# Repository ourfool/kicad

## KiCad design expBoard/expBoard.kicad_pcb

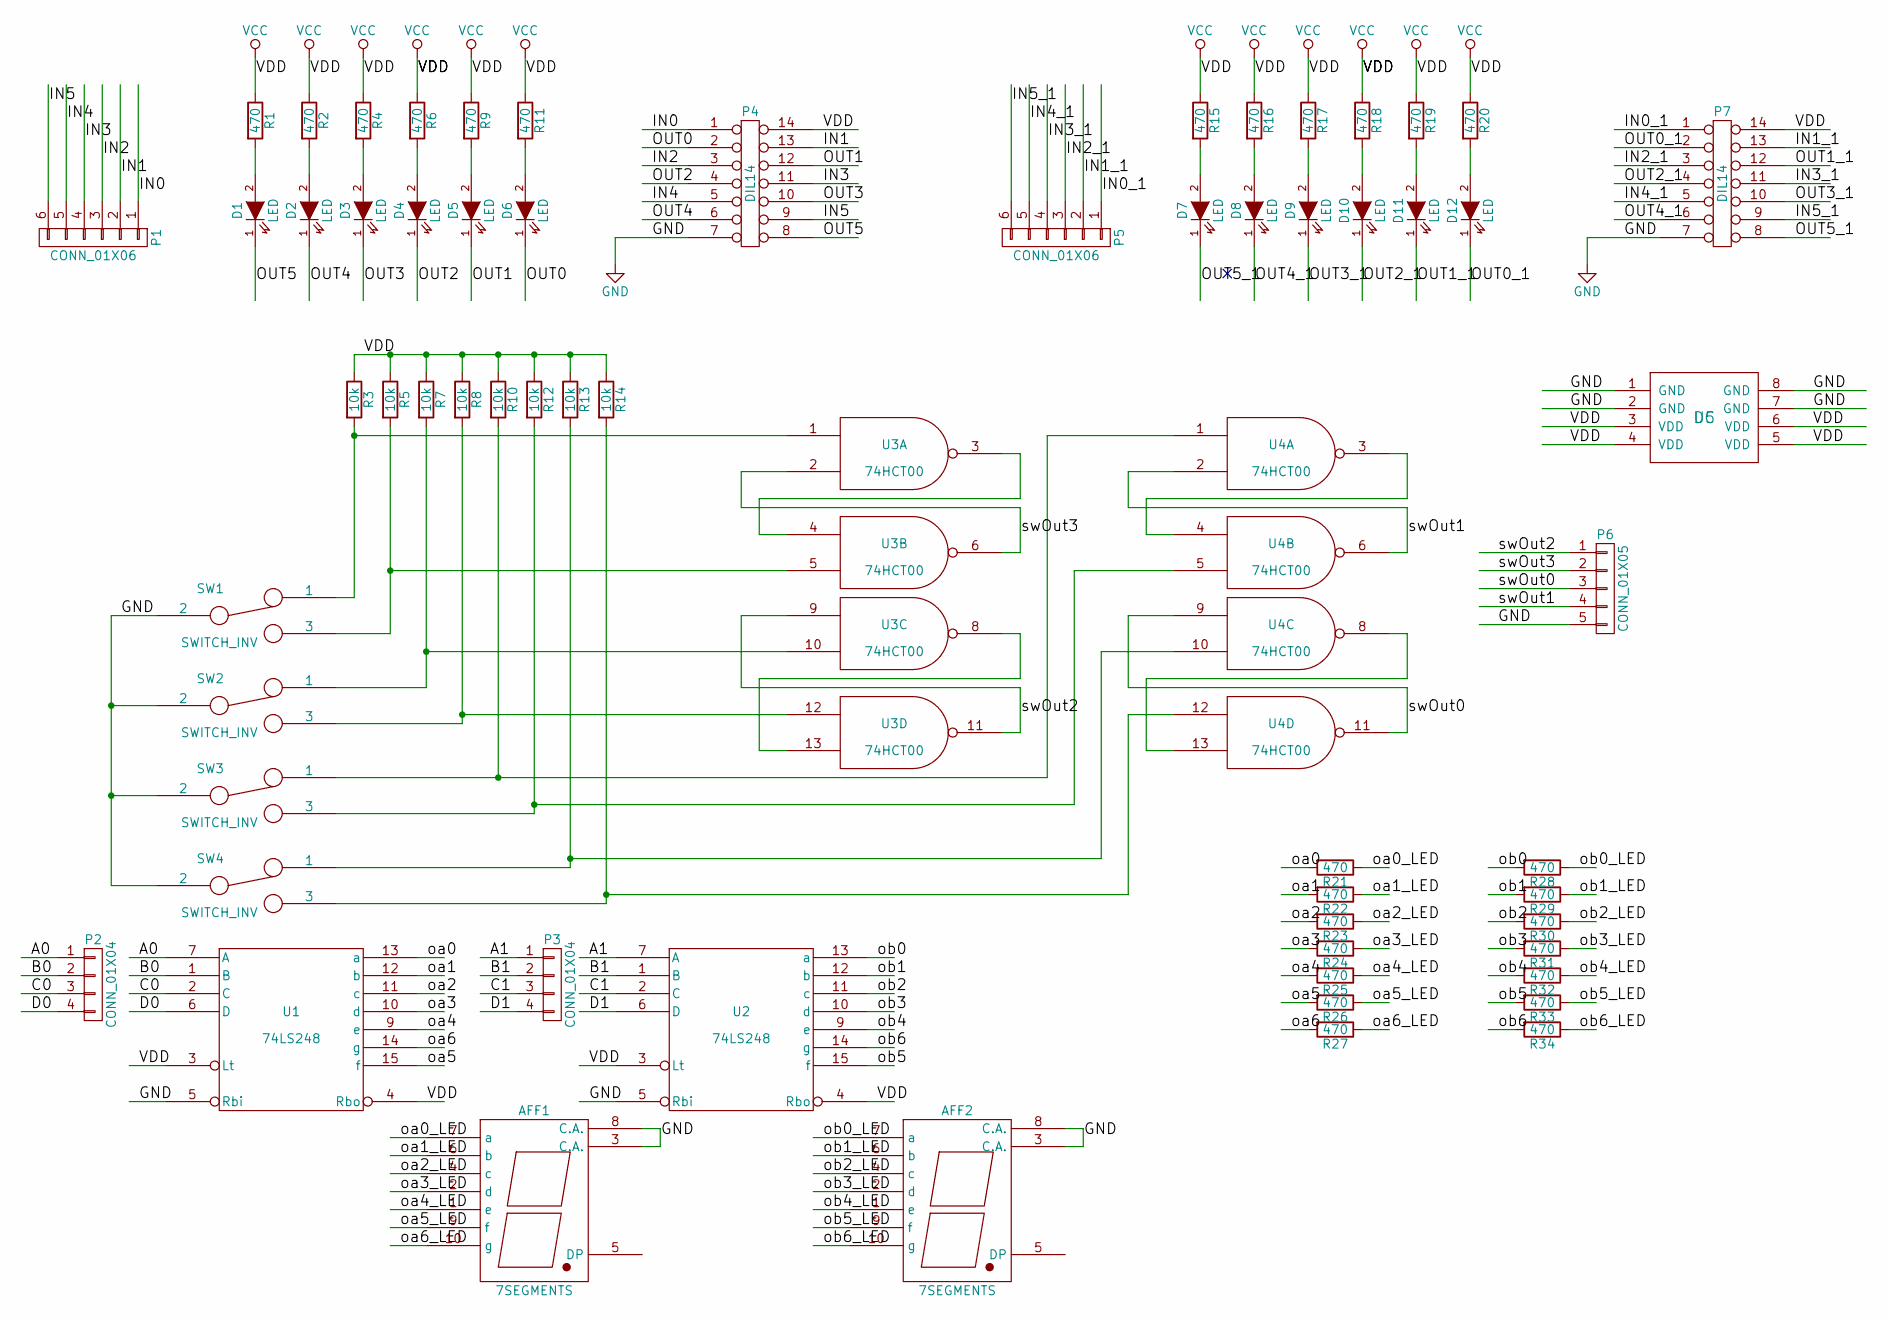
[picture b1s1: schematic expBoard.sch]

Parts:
AFF1, AFF2: 7SEGMENTS; 7SegmentLED_LTS6760_LTS6780
D1, D2, D3, D4, D5, D6, D7, D8, D9, D10, D11, D12: LED; D_A-405_P2.54mm_Vertical_KathodeUp
P1, P5: CONN_01X06; Pin_Header_Straight_1x06_Pitch2.54mm
P2, P3: CONN_01X04; Pin_Header_Straight_1x04_Pitch2.54mm
P4, P7: DIL14; DIP-14_W7.62mm
P6: CONN_01X05; Pin_Header_Straight_1x05_Pitch2.54mm
R1, R2, R4, R6, R9, R11, R15, R16, R17, R18, R19, R20, R21, R22, R23, R24, R25, R26, R27, R28, R29, R30, R31, R32, R33, R34: 470; R_Axial_DIN0207_L6.3mm_D2.5mm_P10.16mm_Horizontal
R3, R5, R7, R8, R10, R12, R13, R14: 10k; R_Axial_DIN0207_L6.3mm_D2.5mm_P10.16mm_Horizontal
SW1, SW2, SW3, SW4: SWITCH_INV; Pin_Header_Straight_1x03_Pitch2.54mm
U1, U2: 74LS248; DIP-16_W7.62mm_Socket
U3, U4: 74HCT00; DIP-14_W7.62mm
U5: DC

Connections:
/A0: P2.1, U1.7 (A)
/A1: P3.1, U2.7 (A)
/B0: P2.2, U1.1 (B)
/B1: P3.2, U2.1 (B)
/C0: P2.3, U1.2 (C)
/C1: P3.3, U2.2 (C)
/D0: P2.4, U1.6 (D)
/D1: P3.4, U2.6 (D)
/IN0: P1.1, P4.1
/IN0_1: P5.1, P7.1
/IN1: P1.2, P4.13
/IN1_1: P5.2, P7.13
/IN2: P1.3, P4.3
/IN2_1: P5.3, P7.3
/IN3: P1.4, P4.11
/IN3_1: P5.4, P7.11
/IN4: P1.5, P4.5
/IN4_1: P5.5, P7.5
/IN5: P1.6, P4.9
/IN5_1: P5.6, P7.9
/OUT0: D6.1 (K), P4.2
/OUT0_1: D12.1 (K), P7.2
/OUT1: D5.1 (K), P4.12
/OUT1_1: D11.1 (K), P7.12
/OUT2: D4.1 (K), P4.4
/OUT2_1: D10.1 (K), P7.4
/OUT3: D3.1 (K), P4.10
/OUT3_1: D9.1 (K), P7.10
/OUT4: D2.1 (K), P4.6
/OUT4_1: D8.1 (K), P7.6
/OUT5: D1.1 (K), P4.8
/OUT5_1: D7.1 (K), P7.8
/oa0: R21.2, U1.13 (a)
/oa0_LED: AFF1.7 (a), R21.1
/oa1: R22.2, U1.12 (b)
/oa1_LED: AFF1.6 (b), R22.1
/oa2: R23.2, U1.11 (c)
/oa2_LED: AFF1.4 (c), R23.1
/oa3: R24.2, U1.10 (d)
/oa3_LED: AFF1.2 (d), R24.1
/oa4: R25.2, U1.9 (e)
/oa4_LED: AFF1.1 (e), R25.1
/oa5: R26.2, U1.15 (f)
/oa5_LED: AFF1.9 (f), R26.1
/oa6: R27.2, U1.14 (g)
/oa6_LED: AFF1.10 (g), R27.1
/ob0: R28.2, U2.13 (a)
/ob0_LED: AFF2.7 (a), R28.1
/ob1: R29.2, U2.12 (b)
/ob1_LED: AFF2.6 (b), R29.1
/ob2: R30.2, U2.11 (c)
/ob2_LED: AFF2.4 (c), R30.1
/ob3: R31.2, U2.10 (d)
/ob3_LED: AFF2.2 (d), R31.1
/ob4: R32.2, U2.9 (e)
/ob4_LED: AFF2.1 (e), R32.1
/ob5: R33.2, U2.15 (f)
/ob5_LED: AFF2.9 (f), R33.1
/ob6: R34.2, U2.14 (g)
/ob6_LED: AFF2.10 (g), R34.1
/swOut0: P6.3, U4.9, U4.11
/swOut1: P6.4, U4.2, U4.6
/swOut2: P6.1, U3.9, U3.11
/swOut3: P6.2, U3.2, U3.6
GND: AFF1.3 (C.A.), AFF1.8 (C.A.), AFF2.3 (C.A.), AFF2.8 (C.A.), P4.7, P6.5, P7.7, SW1.2, SW2.2, SW3.2, SW4.2, U1.5 (Rbi), U1.8 (GND), U2.5 (Rbi), U2.8 (GND), U3.7 (GND), U4.7 (GND), U5.1 (GND), U5.2 (GND), U5.7 (GND), U5.8 (GND)
unnamed: D1.2 (A), R1.2
unnamed: D2.2 (A), R2.2
unnamed: D3.2 (A), R4.2
unnamed: D4.2 (A), R6.2
unnamed: D5.2 (A), R9.2
unnamed: D6.2 (A), R11.2
unnamed: D7.2 (A), R15.2
unnamed: D8.2 (A), R16.2
unnamed: D9.2 (A), R17.2
unnamed: D10.2 (A), R18.2
unnamed: D11.2 (A), R19.2
unnamed: D12.2 (A), R20.2
unnamed: R3.2, SW1.1, U3.1
unnamed: R5.2, SW1.3, U3.5
unnamed: R7.2, SW2.1, U3.10
unnamed: R8.2, SW2.3, U3.12
unnamed: R10.2, SW3.1, U4.1
unnamed: R12.2, SW3.3, U4.5
unnamed: R13.2, SW4.1, U4.10
unnamed: R14.2, SW4.3, U4.12
unnamed: U3.3, U3.4
unnamed: U3.8, U3.13
unnamed: U4.3, U4.4
unnamed: U4.8, U4.13
VCC: P4.14, P7.14, R1.1, R2.1, R3.1, R4.1, R5.1, R6.1, R7.1, R8.1, R9.1, R10.1, R11.1, R12.1, R13.1, R14.1, R15.1, R16.1, R17.1, R18.1, R19.1, R20.1, U1.3 (Lt), U1.4 (Rbo), U1.16 (VCC), U2.3 (Lt), U2.4 (Rbo), U2.16 (VCC), U3.14 (VCC), U4.14 (VCC), U5.3 (VDD), U5.4 (VDD), U5.5 (VDD), U5.6 (VDD)

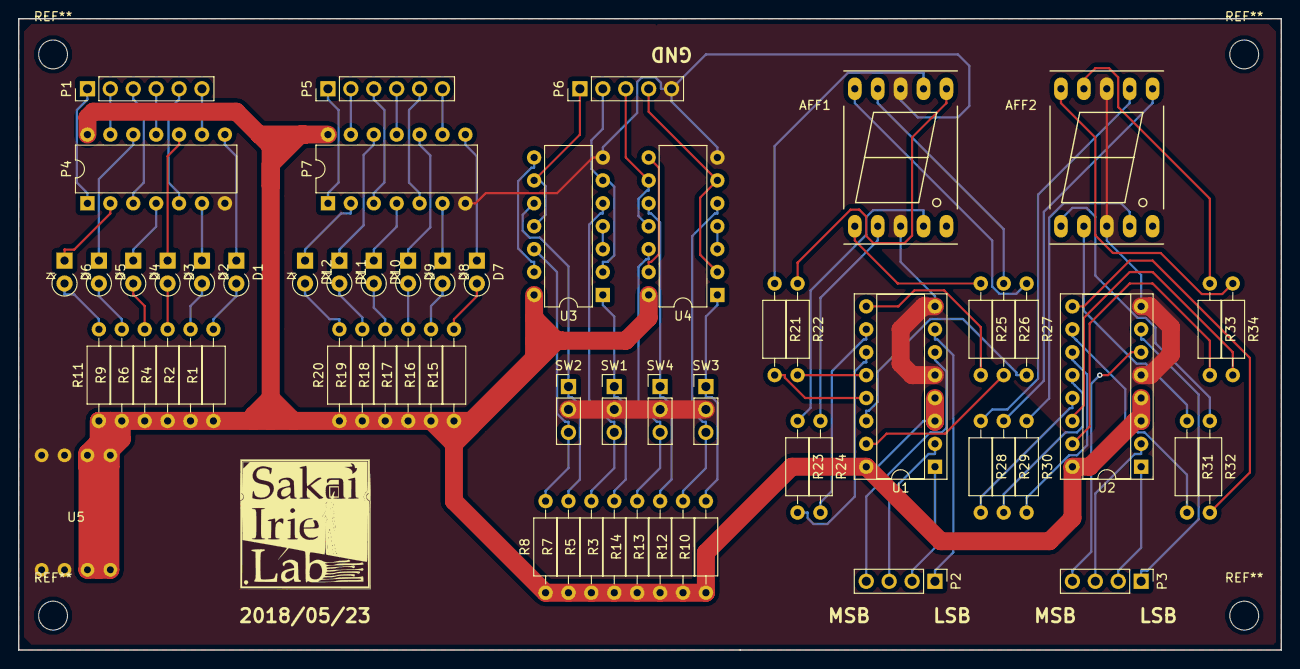
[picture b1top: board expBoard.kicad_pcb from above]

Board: 2 copper layers, 140.0 x 70.0 mm, 64 parts (0 on the bottom side), 90 nets.

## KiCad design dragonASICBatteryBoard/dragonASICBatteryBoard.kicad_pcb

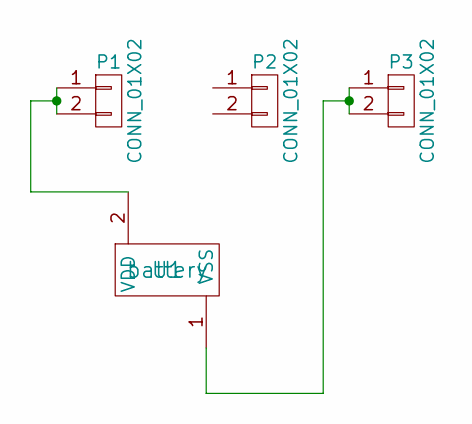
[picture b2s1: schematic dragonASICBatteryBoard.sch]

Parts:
P1, P2, P3: CONN_01X02; Pin_Header_Straight_1x02_Pitch2.54mm
U1: battery

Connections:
unnamed: P1.1, P1.2, U1.2 (VDD)
unnamed: P3.1, P3.2, U1.1 (VSS)

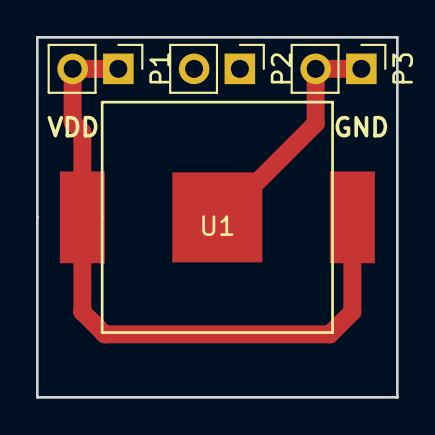
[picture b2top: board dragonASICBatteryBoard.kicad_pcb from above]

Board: 2 copper layers, 20.0 x 20.0 mm, 4 parts (0 on the bottom side), 2 nets.

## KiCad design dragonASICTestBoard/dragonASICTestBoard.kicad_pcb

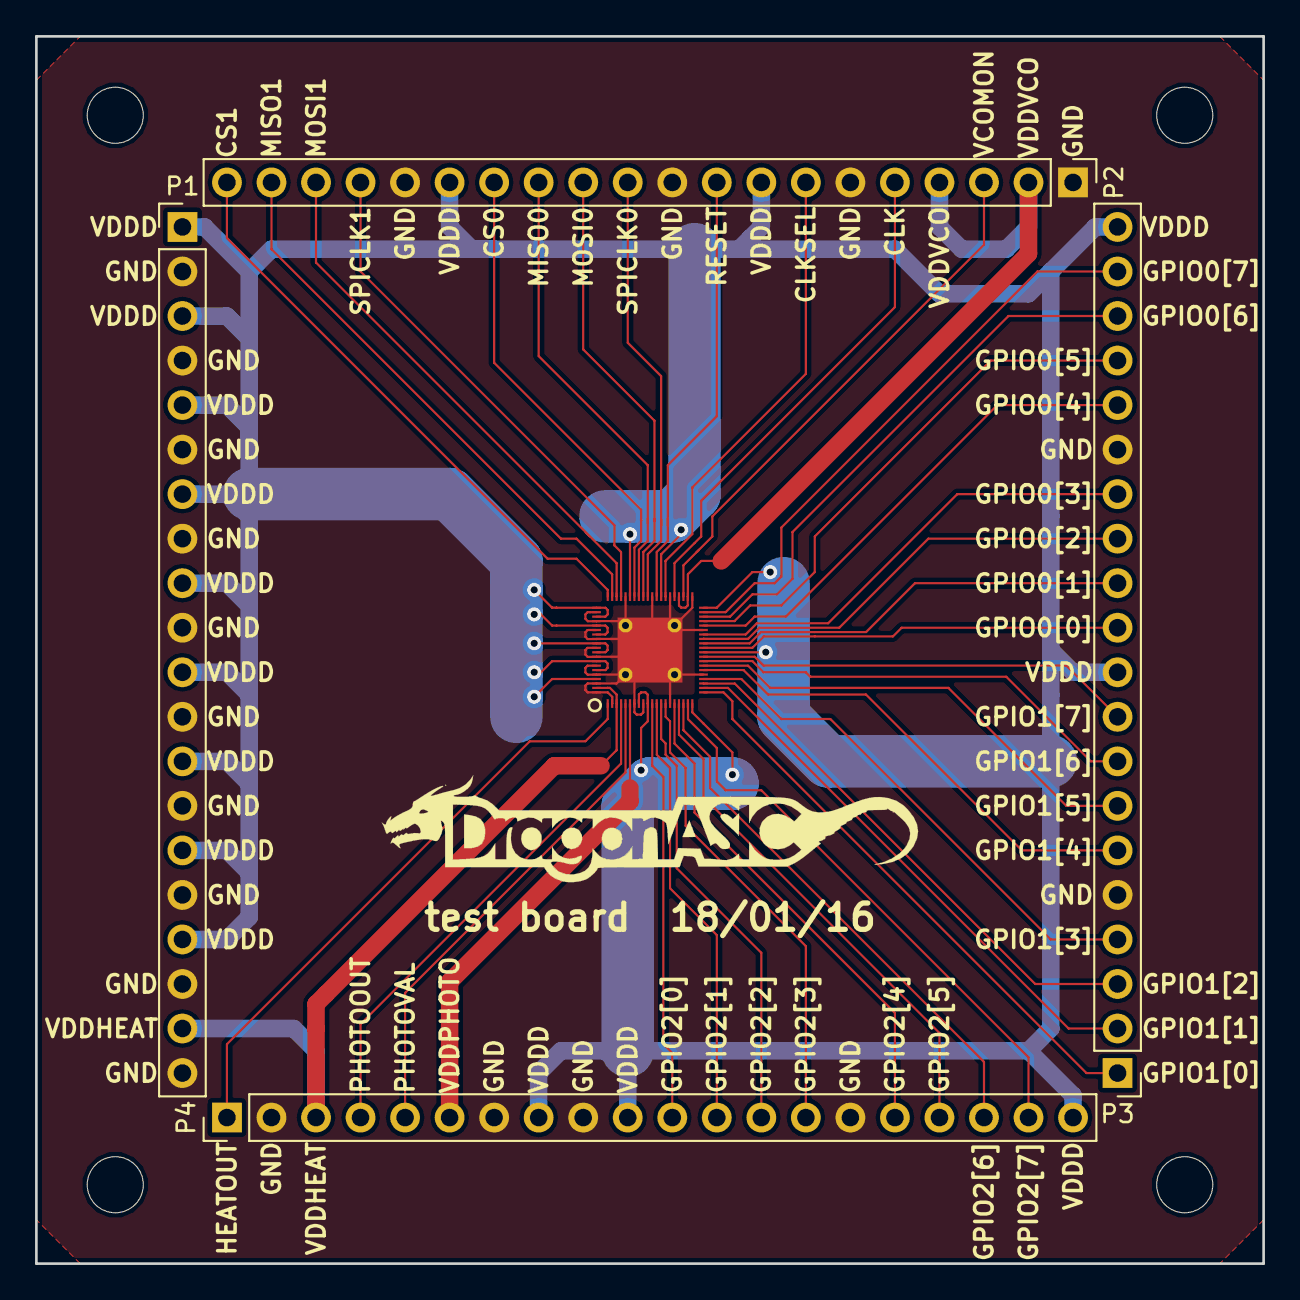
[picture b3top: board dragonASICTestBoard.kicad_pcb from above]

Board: 2 copper layers, 70.0 x 70.0 mm, 4 parts (0 on the bottom side), 4 nets.

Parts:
P1, P2, P3, P4: CONN_01X20; Pin_Header_Straight_1x20_Pitch2.54mm

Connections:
/VDD: P1.1, P1.3, P1.5, P1.7, P1.9, P1.11, P1.13, P1.15, P1.17, P2.8, P2.15, P3.10, P3.20, P4.8, P4.10, P4.20
/VDDHEAT: P1.19, P4.3
/VDDVCO: P2.2, P2.4
GND: P1.2, P1.4, P1.6, P1.8, P1.10, P1.12, P1.14, P1.16, P1.18, P1.20, P2.1, P2.6, P2.10, P2.16, P3.5, P3.15, P4.2, P4.7, P4.9, P4.15

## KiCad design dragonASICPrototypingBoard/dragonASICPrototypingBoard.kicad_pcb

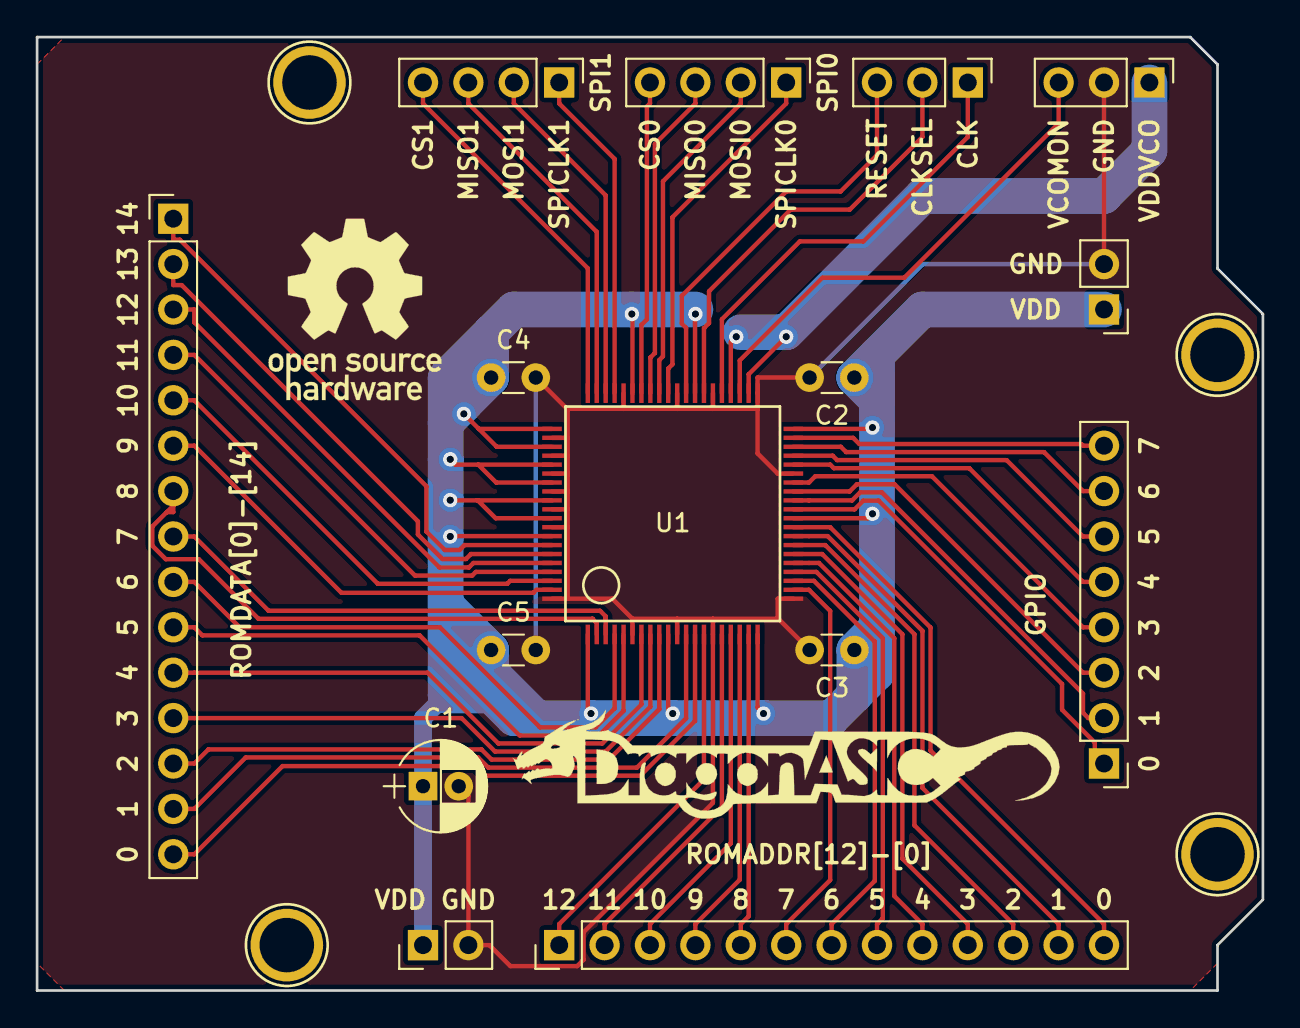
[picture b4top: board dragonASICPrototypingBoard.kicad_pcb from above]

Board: 2 copper layers, 68.6 x 53.3 mm, 12 parts (0 on the bottom side), 11 nets.

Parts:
C1: CP; CP_Radial_D5.0mm_P2.00mm
C2, C3, C4, C5: C; C_Disc_D3.0mm_W1.6mm_P2.50mm
P5, P6, P7, P8: CONN_1; Arduino_1pin
SPI0, SPI1: CONN_01X04; Pin_Header_Straight_1x04_Pitch2.54mm
U1: QFP80

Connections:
/CS0: SPI0.4, U1.54
/CS1: SPI1.4, U1.60
/GND: C1.2, C2.2, C3.2, C4.2, C5.2, U1.6, U1.11, U1.15, U1.21, U1.35, U1.41, U1.46, U1.50, U1.56, U1.62, U1.64, U1.66, U1.68, U1.70, U1.72, U1.80
/MISO0: SPI0.3, U1.53
/MISO1: SPI1.3, U1.59
/MOSI0: SPI0.2, U1.52
/MOSI1: SPI1.2, U1.58
/SPICLK0: SPI0.1, U1.51
/SPICLK1: SPI1.1, U1.57
/VDD: C1.1, C2.1, C3.1, C4.1, C5.1, U1.1, U1.10, U1.20, U1.30, U1.40, U1.48, U1.55, U1.61, U1.63, U1.65, U1.67, U1.69, U1.71, U1.73
unnamed: U1.42, U1.44

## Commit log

2018-01-14 Add dragonASICTestBoard
2018-01-14 Add schematic and layout to dragonASICTestBoard
2018-01-15 Add PCB layout to dragonASICTestBoard
2018-01-16 Fix PCB layout of dragonASICTestBoard
2018-01-18 Add dragonASICPrototypingBoard
2018-01-19 Add PCB layout to dragonASICPrototypingBoard
2018-01-21 Add dragonASICSolarCellBoard
2018-01-22 Add PCB layout to dragonASICSolarCellBoard
2018-01-22 Add dragonASICBatteryBoard
2018-01-23 add dragonASICSensorBoard
2018-01-25 Add PCB layout to dragonASICSensorBoard
2018-05-24 Add expBoard
2018-05-24 Revert "Add expBoard"
    This reverts commit c198c0ad4dfa7197c7019bebcc7fc89455b649b5.
2018-05-25 Fix PCB layout of expBoard
